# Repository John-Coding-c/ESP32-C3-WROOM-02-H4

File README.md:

# ESP32IoT sensor board

A compact, battery-powered, Wi-Fi/Bluetooth LE sensor board built around the
**ESP32-C3-WROOM-02-H4**. It logs temperature, humidity, pressure, light and sound,
stores data on a microSD card and external flash, and charges a single-cell LiPo
from USB-C. The same USB-C port programs the ESP32 automatically.

## Features

**Board**
- 4-layer PCB, 1.6 mm thick, **90 x 53 mm**
- 90 components, 79 nets, 985 track segments, 167 vias
- Single-sided assembly (all parts on the top side), 0805 passives

**Processing and wireless**
- ESP32-C3-WROOM-02-H4: 32-bit RISC-V at up to 160 MHz, 4 MB flash, 2.4 GHz Wi-Fi (802.11 b/g/n) and Bluetooth 5 LE, on-module antenna
- Extra W25Q32JVSSIQ SPI flash: 32 Mbit (4 MB)
- microSD slot on the SPI bus, with test points on MOSI, MISO, SCLK, CS and CS_SD

**Sensors**
- BME280: temperature, humidity and barometric pressure over I2C (4.7 kOhm pull-ups on SDA/SCL)
- TEMT6000X01 ambient-light phototransistor, read on an ADC pin
- CMC-5042PF-AC electret microphone with a MAX4466 amplifier and a 100 kOhm gain trimmer (R17)

**Power**
- USB-C input, 5 V, with a 1.1 A resettable fuse (F1) and USBLC6-2SC6 ESD protection on D+/D-
- MCP73871 LiPo charger with power-path management: fast-charge current about 500 mA (R5 = 2 kOhm), status on 3 LEDs (charging, charged, power good)
- LM1117-3.3 regulator, 800 mA rating, feeding the 3.3 V rail
- JST-PH 2 mm connector for a single-cell LiPo
- Ferrite bead (FB1) between the charger output and the 5 V rail

**USB and programming**
- CP2102N USB-to-UART bridge
- Auto-reset and auto-boot circuit (2 BC817 transistors on DTR/RTS) so the ESP32 programs over USB with no button presses
- EN (reset) and BOOT push-buttons

**Expansion and indicators**
- 4-pin I2C header (3V3, GND, SDA, SCL)
- 5-pin GPIO header (GPIO8, GPIO18, GPIO19, 3V3, GND)
- 6 LEDs: 3 charger status, 1 power, 1 UART TX, 1 UART RX
- 5 test points for the SPI signals

## Gallery

| Top | Bottom |
|---|---|
|  |  |

## Schematics

| Sheet | File |
|---|---|
| Power, charger and regulator | [01-power-and-charging.png](docs/schematics/01-power-and-charging.png) |
| ESP32-C3, USB bridge, flash, SD card | [02-esp32-c3-and-usb.png](docs/schematics/02-esp32-c3-and-usb.png) |
| Sensors (BME280, light, microphone) | [03-sensors.png](docs/schematics/03-sensors.png) |
| User interface (buttons, auto-reset, headers) | [04-user-interface.png](docs/schematics/04-user-interface.png) |

### Power and charging

### ESP32-C3, USB and storage

### Sensors

### User interface

## Direct Memory Access

uses the ESP32-C3's DMA for the SPI flash, the microSD card and the light sensor. 

```
cd firmware
idf.py set-target esp32c3
idf.py build flash monitor
```

## Project files

| Path | Contents |
|---|---|
| `ESP32IoT.kicad_pro` | KiCad 10 project |
| `ESP32IoT.kicad_sch` + `esp32-c3-02`, `sensors`, `user_interface` sheets | Hierarchical schematic |
| `ESP32IoT.kicad_pcb` | Routed 4-layer board |
| `Symbols/`, `Footprints/`, `3D models/` | Project libraries |
| `firmware/` | ESP-IDF test firmware using GDMA (SPI flash, SD card, ADC) |
| `BOM.ods`, `BOM11.xlsx` | Bill of materials |
| `docs/` | Renders and schematic images used by this README (`docs/schematics/ESP32IoT-schematic.pdf` is the full vector schematic) |

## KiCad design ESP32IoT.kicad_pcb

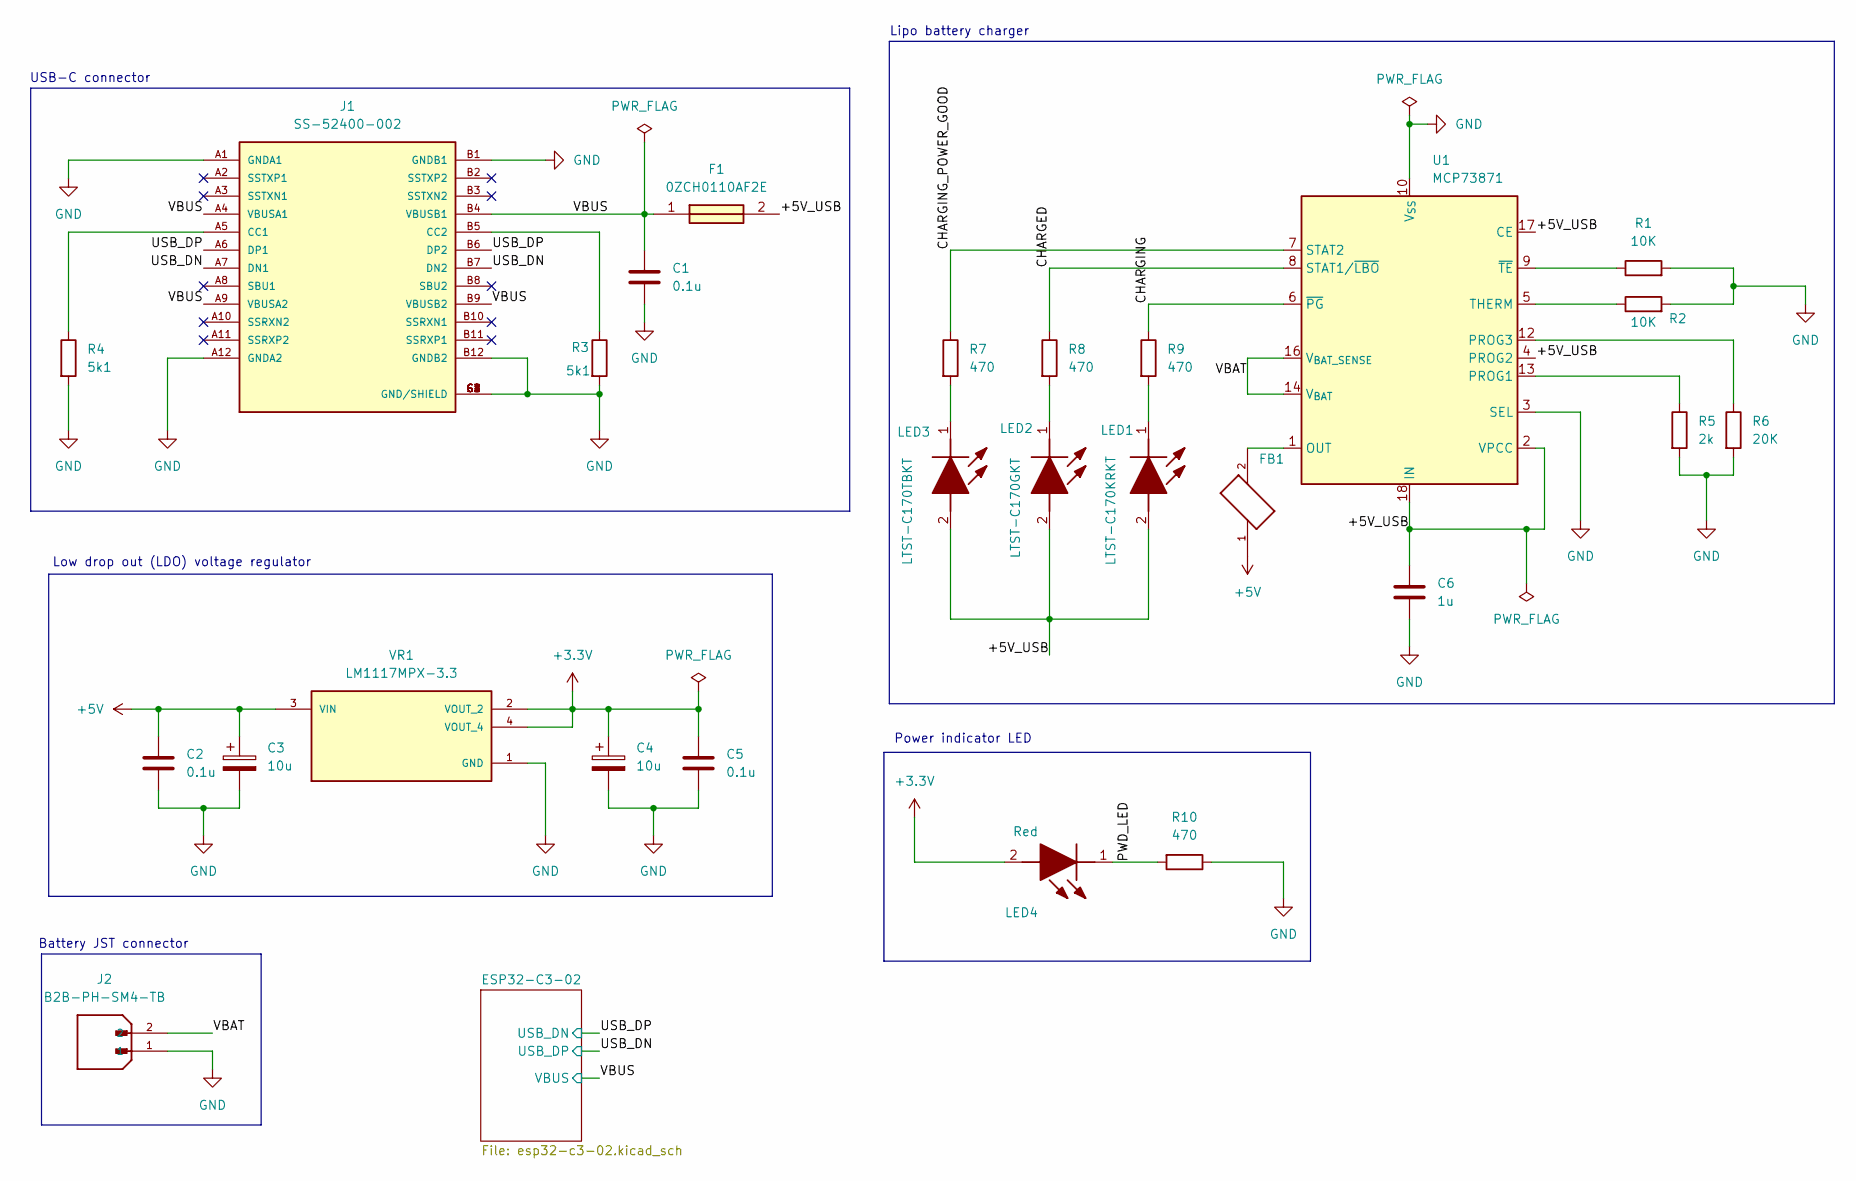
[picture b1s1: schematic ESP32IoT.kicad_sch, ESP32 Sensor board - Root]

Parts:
C1, C2, C5: 0.1u; C_0805_2012Metric
C3, C4: 10u; T491A
C6: 1u; C_0805_2012Metric
F1: 0ZCH0110AF2E; FUSC3226X100N; Manufacturer_Part_Number 0ZCH0110AF2E
FB1: FBMJ2125HM330-T; BEADC2012X105N
J1: SS-52400-002; BELFUSE_SS-52400-002; PARTREV A0
J2: B2B-PH-SM4-TB; JST_B2B-PH-SM4-TB; PARTREV N/A
LED1: LTST-C170KRKT; LEDC2012X120N; Manufacturer_Part_Number LTST-C170KRKT; Mouser Part Number 859-LTST-C170KRKT
LED2: LTST-C170GKT; LEDC2012X120N; Manufacturer_Part_Number LTST-C170GKT; Mouser Part Number 859-LTST-C170GKT
LED3: LTST-C170TBKT; LEDC2012X120N; Manufacturer_Part_Number LTST-C170TBKT; Mouser Part Number 859-LTST-C170TBKT
LED4: Red; LEDC2012X120N; Manufacturer_Part_Number LTST-C170KRKT; Mouser Part Number 859-LTST-C170KRKT
R1, R2: 10K; R_0805_2012Metric
R3, R4: 5k1; R_0805_2012Metric
R5: 2k; R_0805_2012Metric
R6: 20K; R_0805_2012Metric
R7, R8, R9, R10: 470; R_0805_2012Metric
U1: MCP73871; QFN-20-1EP_4x4mm_P0.5mm_EP2.5x2.5mm
VR1: LM1117MPX-3.3; VREG_LM1117MPX-3.3

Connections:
+3.3V: C4.1, C5.1, LED4.2 (A), VR1.2 (VOUT_2), VR1.4 (VOUT_4); also elsewhere on the board
+5V: C2.1, C3.1, FB1.1, VR1.3 (VIN)
/+5V_USB: C6.1, F1.2, LED1.2 (A), LED2.2 (A), LED3.2 (A), U1.2 (VPCC), U1.4 (PROG2), U1.17 (CE), U1.18 (IN), U1.19 (IN)
/CHARGED: R8.1, U1.8 (STAT1/~LBO)
/CHARGING: R9.1, U1.6 (~PG)
/CHARGING_POWER_GOOD: R7.1, U1.7 (STAT2)
/PWD_LED: LED4.1 (K), R10.2
/USB_DN: J1.A7 (DN1), J1.B7 (DN2); also elsewhere on the board
/USB_DP: J1.A6 (DP1), J1.B6 (DP2); also elsewhere on the board
/VBAT: J2.2, U1.14 (V_{BAT}), U1.15 (V_{BAT}), U1.16 (V_{BAT_SENSE})
/VBUS: C1.1, F1.1, J1.A4 (VBUSA1), J1.A9 (VBUSA2), J1.B4 (VBUSB1), J1.B9 (VBUSB2); also elsewhere on the board
GND: C1.2, C2.2, C3.2, C4.2, C5.2, C6.2, J1.A1 (GNDA1), J1.A12 (GNDA2), J1.B1 (GNDB1), J1.B12 (GNDB2), J1.G1 (GND/SHIELD), J1.G2 (GND/SHIELD), J1.G3 (GND/SHIELD), J1.G4 (GND/SHIELD), J1.S1 (GND/SHIELD), J1.S2 (GND/SHIELD), J1.S3 (GND/SHIELD), J1.S4 (GND/SHIELD), J2.1, R1.2, R2.2, R3.2, R4.2, R5.2, R6.2, R10.1, U1.3 (SEL), U1.10 (V_{SS}), U1.11 (V_{SS}), U1.21 (V_{SS}), VR1.1 (GND); also elsewhere on the board
unnamed: FB1.2, U1.1 (OUT), U1.20 (OUT)
unnamed: J1.A5 (CC1), R4.1
unnamed: J1.B5 (CC2), R3.1
unnamed: LED1.1 (K), R9.2
unnamed: LED2.1 (K), R8.2
unnamed: LED3.1 (K), R7.2
unnamed: R5.1, U1.13 (PROG1)
unnamed: R6.1, U1.12 (PROG3)
unnamed: R2.1, U1.5 (THERM)
unnamed: R1.1, U1.9 (~TE)

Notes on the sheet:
USB-C connector
Power indicator LED
Lipo battery charger
Battery JST connector
Low drop out (LDO) voltage regulator

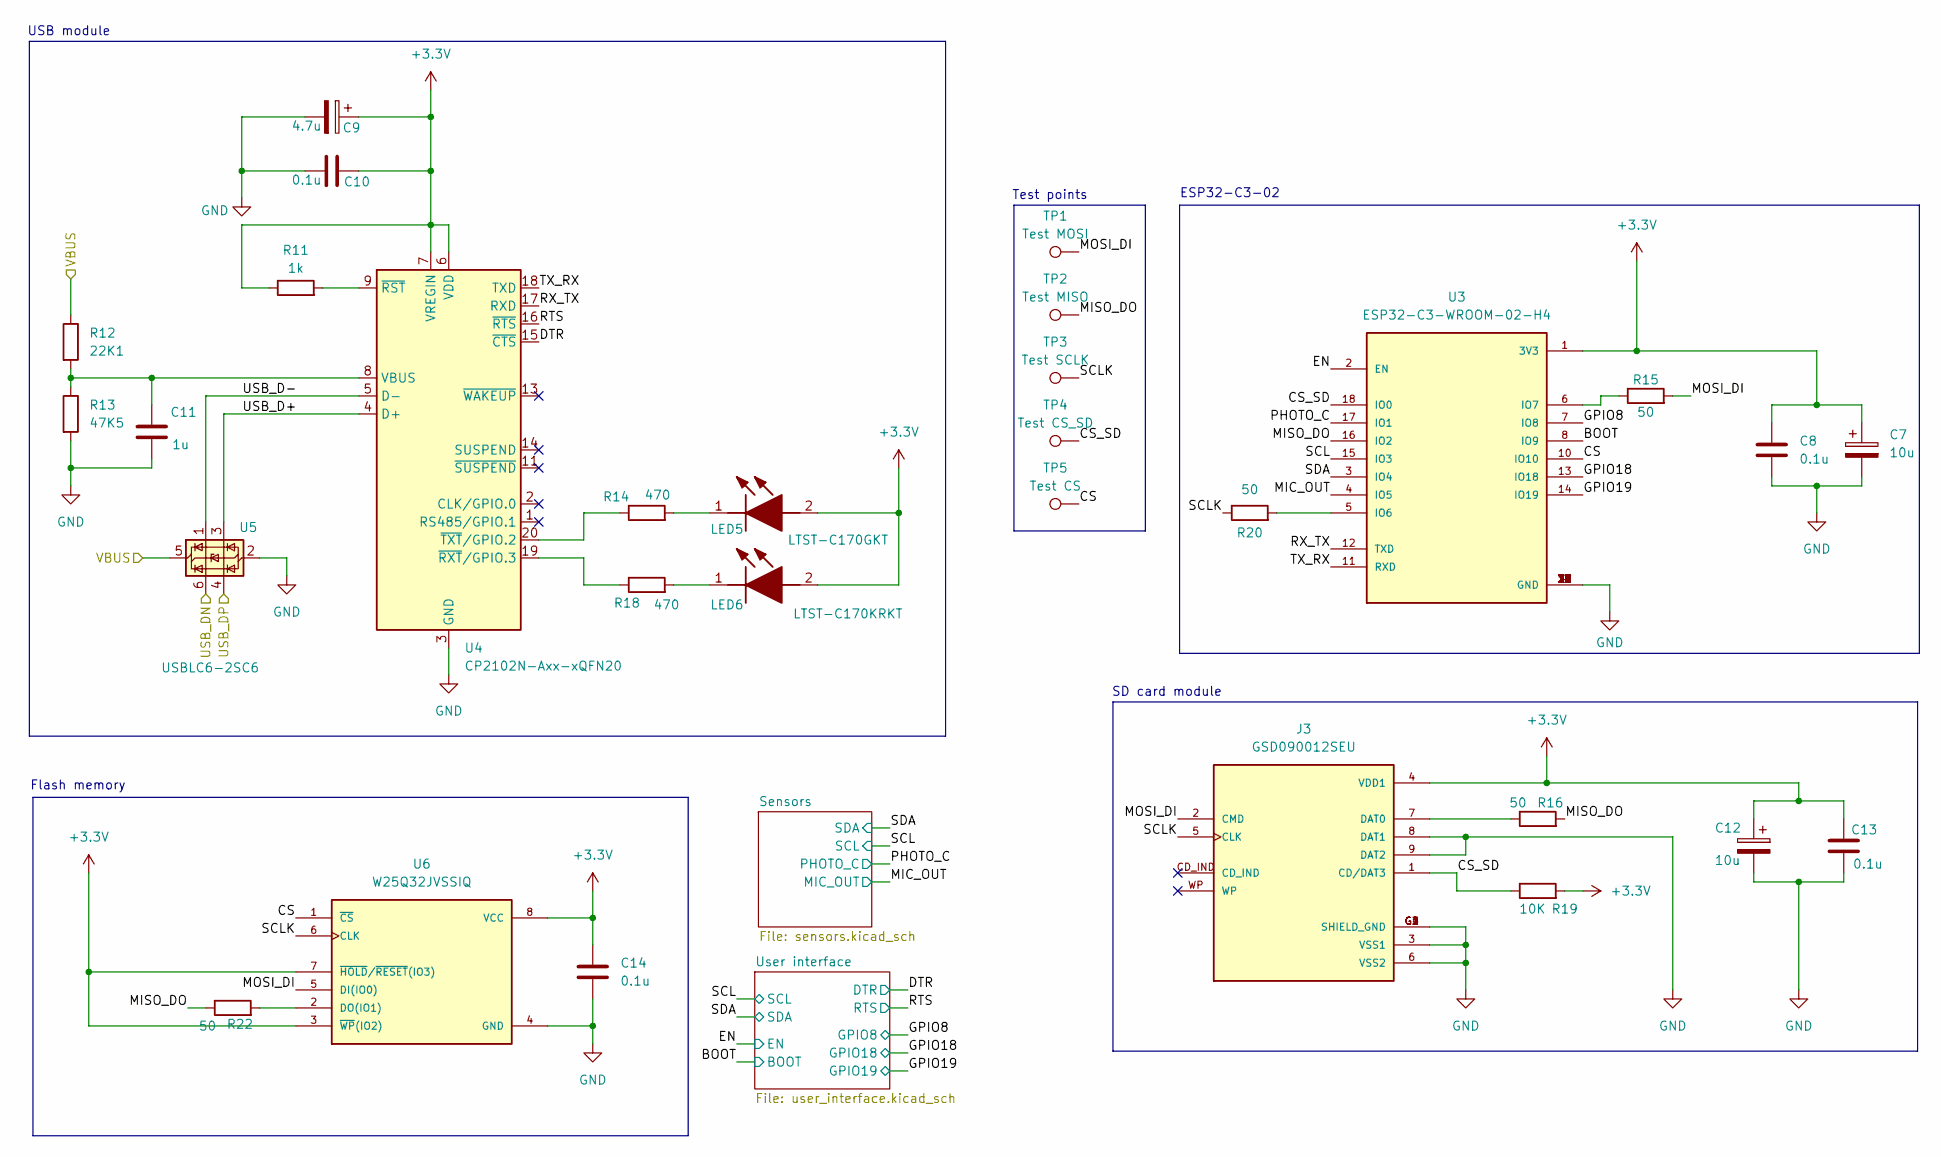
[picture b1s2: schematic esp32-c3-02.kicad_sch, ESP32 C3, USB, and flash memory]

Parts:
C7, C12: 10u; T491A
C8, C10, C13, C14: 0.1u; C_0805_2012Metric
C9: 4.7u; T491A
C11: 1u; C_0805_2012Metric
J3: GSD090012SEU; AMPHENOL_GSD090012SEU; PARTREV E
LED5: LTST-C170GKT; LEDC2012X120N; Manufacturer_Part_Number LTST-C170GKT; Mouser Part Number 859-LTST-C170GKT
LED6: LTST-C170KRKT; LEDC2012X120N; Manufacturer_Part_Number LTST-C170KRKT; Mouser Part Number 859-LTST-C170KRKT
R11: 1k; R_0805_2012Metric
R12: 22K1; R_0805_2012Metric
R13: 47K5; R_0805_2012Metric
R14, R18: 470; R_0805_2012Metric
R15, R16, R20, R22: 50; R_0805_2012Metric
R19: 10K; R_0805_2012Metric
TP1: Test MOSI; TestPoint_Pad_D1.0mm
TP2: Test MISO; TestPoint_Pad_D1.0mm
TP3: Test SCLK; TestPoint_Pad_D1.0mm
TP4: Test CS_SD; TestPoint_Pad_D1.0mm
TP5: Test CS; TestPoint_Pad_D1.0mm
U3: ESP32-C3-WROOM-02-H4; MODULE_ESP32-C3-WROOM-02-H4
U4: CP2102N-Axx-xQFN20; SiliconLabs_QFN-20-1EP_3x3mm_P0.5mm_EP1.8x1.8mm
U5: USBLC6-2SC6; SOT-23-6
U6: W25Q32JVSSIQ; SOIC127P790X216-8N; M_PART_NUMBER W25QXX

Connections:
+3.3V: C7.1, C8.1, C9.1, C10.2, C12.1, C13.1, C14.1, J3.4 (VDD1), LED5.2 (A), LED6.2 (A), R11.1, R19.2, U3.1 (3V3), U4.6 (VDD), U4.7 (VREGIN), U6.3 (~WP(IO2)), U6.7 (~HOLD/~RESET(IO3)), U6.8 (VCC); also elsewhere on the board
/ESP32-C3-02/BOOT: U3.8 (IO9); also elsewhere on the board
/ESP32-C3-02/CS: TP5.1 (1_1), U3.10 (IO10), U6.1 (~CS)
/ESP32-C3-02/CS_SD: J3.1 (CD/DAT3), R19.1, TP4.1 (1_1), U3.18 (IO0)
/ESP32-C3-02/DTR: U4.15 (~CTS); also elsewhere on the board
/ESP32-C3-02/EN: U3.2 (EN); also elsewhere on the board
/ESP32-C3-02/GPIO8: U3.7 (IO8); also elsewhere on the board
/ESP32-C3-02/GPIO18: U3.13 (IO18); also elsewhere on the board
/ESP32-C3-02/GPIO19: U3.14 (IO19); also elsewhere on the board
/ESP32-C3-02/MIC_OUT: U3.4 (IO5); also elsewhere on the board
/ESP32-C3-02/MISO_DO: R16.2, R22.1, TP2.1 (1_1), U3.16 (IO2)
/ESP32-C3-02/MOSI_DI: J3.2 (CMD), R15.2, TP1.1 (1_1), U6.5 (DI(IO0))
/ESP32-C3-02/PHOTO_C: U3.17 (IO1); also elsewhere on the board
/ESP32-C3-02/RTS: U4.16 (~RTS); also elsewhere on the board
/ESP32-C3-02/RX_TX: U3.12 (TXD), U4.17 (RXD)
/ESP32-C3-02/SCL: U3.15 (IO3); also elsewhere on the board
/ESP32-C3-02/SCLK: J3.5 (CLK), R20.1, TP3.1 (1_1), U6.6 (CLK)
/ESP32-C3-02/SDA: U3.3 (IO4); also elsewhere on the board
/ESP32-C3-02/TX_RX: U3.11 (RXD), U4.18 (TXD)
/ESP32-C3-02/USB_D+: U4.4 (D+), U5.3 (I/O2)
/ESP32-C3-02/USB_D-: U4.5 (D-), U5.1 (I/O1)
/USB_DN: U5.4 (I/O2); also elsewhere on the board
/USB_DP: U5.6 (I/O1); also elsewhere on the board
/VBUS: R12.1, U5.5 (VBUS); also elsewhere on the board
GND: C7.2, C8.2, C9.2, C10.1, C11.2, C12.2, C13.2, C14.2, J3.3 (VSS1), J3.6 (VSS2), J3.8 (DAT1), J3.9 (DAT2), J3.G1 (SHIELD_GND), J3.G2 (SHIELD_GND), J3.G3 (SHIELD_GND), J3.G4 (SHIELD_GND), R13.2, U3.9 (GND), U3.19 (GND), U3.20 (GND), U3.21 (GND), U3.22 (GND), U3.23 (GND), U3.24 (GND), U3.25 (GND), U3.26 (GND), U3.27 (GND), U3.28 (GND), U3.29 (GND), U3.30 (GND), U3.31 (GND), U3.32 (GND), U3.33 (GND), U3.34 (GND), U3.35 (GND), U3.36 (GND), U3.37 (GND), U3.38 (GND), U3.39 (GND), U4.3 (GND), U4.12 (GND), U4.21 (GND), U5.2 (GND), U6.4 (GND); also elsewhere on the board
unnamed: J3.7 (DAT0), R16.1
unnamed: LED5.1 (K), R14.2
unnamed: LED6.1 (K), R18.2
unnamed: R20.2, U3.5 (IO6)
unnamed: R15.1, U3.6 (IO7)
unnamed: C11.1, R12.2, R13.1, U4.8 (VBUS)
unnamed: R11.2, U4.9 (~RST)
unnamed: R18.1, U4.19 (~RXT/GPIO.3)
unnamed: R14.1, U4.20 (~TXT/GPIO.2)
unnamed: R22.2, U6.2 (DO(IO1))

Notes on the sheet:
SD card module
Flash memory
Test points
ESP32-C3-02
USB module

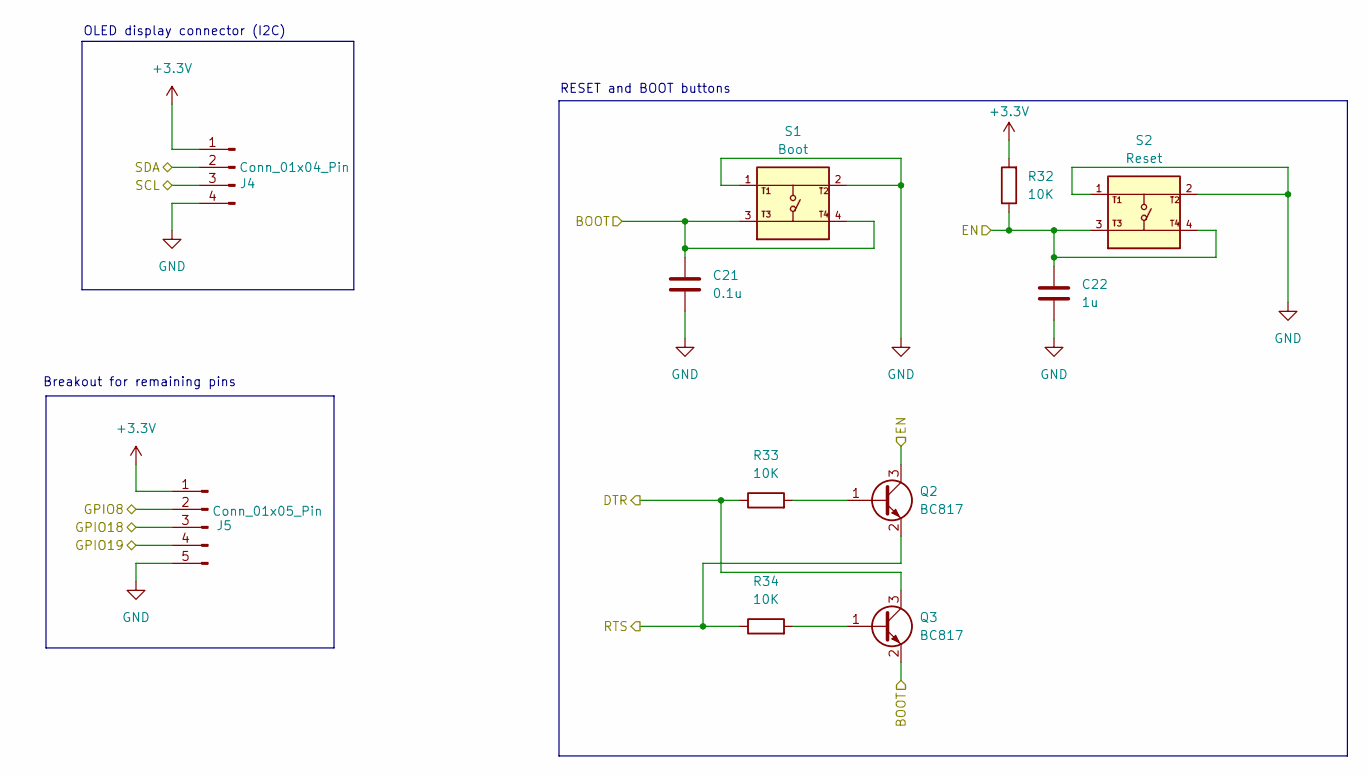
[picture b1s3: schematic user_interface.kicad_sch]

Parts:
C21: 0.1u; C_0805_2012Metric
C22: 1u; C_0805_2012Metric
J4: Conn_01x04_Pin; PinHeader_1x04_P2.54mm_Vertical
J5: Conn_01x05_Pin; PinHeader_1x05_P2.54mm_Vertical
Q2, Q3: BC817; SOT-23
R32, R33, R34: 10K; R_0805_2012Metric
S1: Boot; SW_USLPT2819DT2TR; PARTREV P
S2: Reset; SW_USLPT2819DT2TR; PARTREV P

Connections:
+3.3V: J4.1, J5.1, R32.2; also elsewhere on the board
/ESP32-C3-02/BOOT: C21.1, Q3.2 (E), S1.3, S1.4; also elsewhere on the board
/ESP32-C3-02/DTR: Q3.3 (C), R33.1; also elsewhere on the board
/ESP32-C3-02/EN: C22.1, Q2.3 (C), R32.1, S2.3, S2.4; also elsewhere on the board
/ESP32-C3-02/GPIO8: J5.2; also elsewhere on the board
/ESP32-C3-02/GPIO18: J5.3; also elsewhere on the board
/ESP32-C3-02/GPIO19: J5.4; also elsewhere on the board
/ESP32-C3-02/RTS: Q2.2 (E), R34.1; also elsewhere on the board
/ESP32-C3-02/SCL: J4.3; also elsewhere on the board
/ESP32-C3-02/SDA: J4.2; also elsewhere on the board
GND: C21.2, C22.2, J4.4, J5.5, S1.1, S1.2, S2.1, S2.2; also elsewhere on the board
unnamed: Q2.1 (B), R33.2
unnamed: Q3.1 (B), R34.2

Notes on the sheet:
OLED display connector (I2C)
RESET and BOOT buttons
Breakout for remaining pins

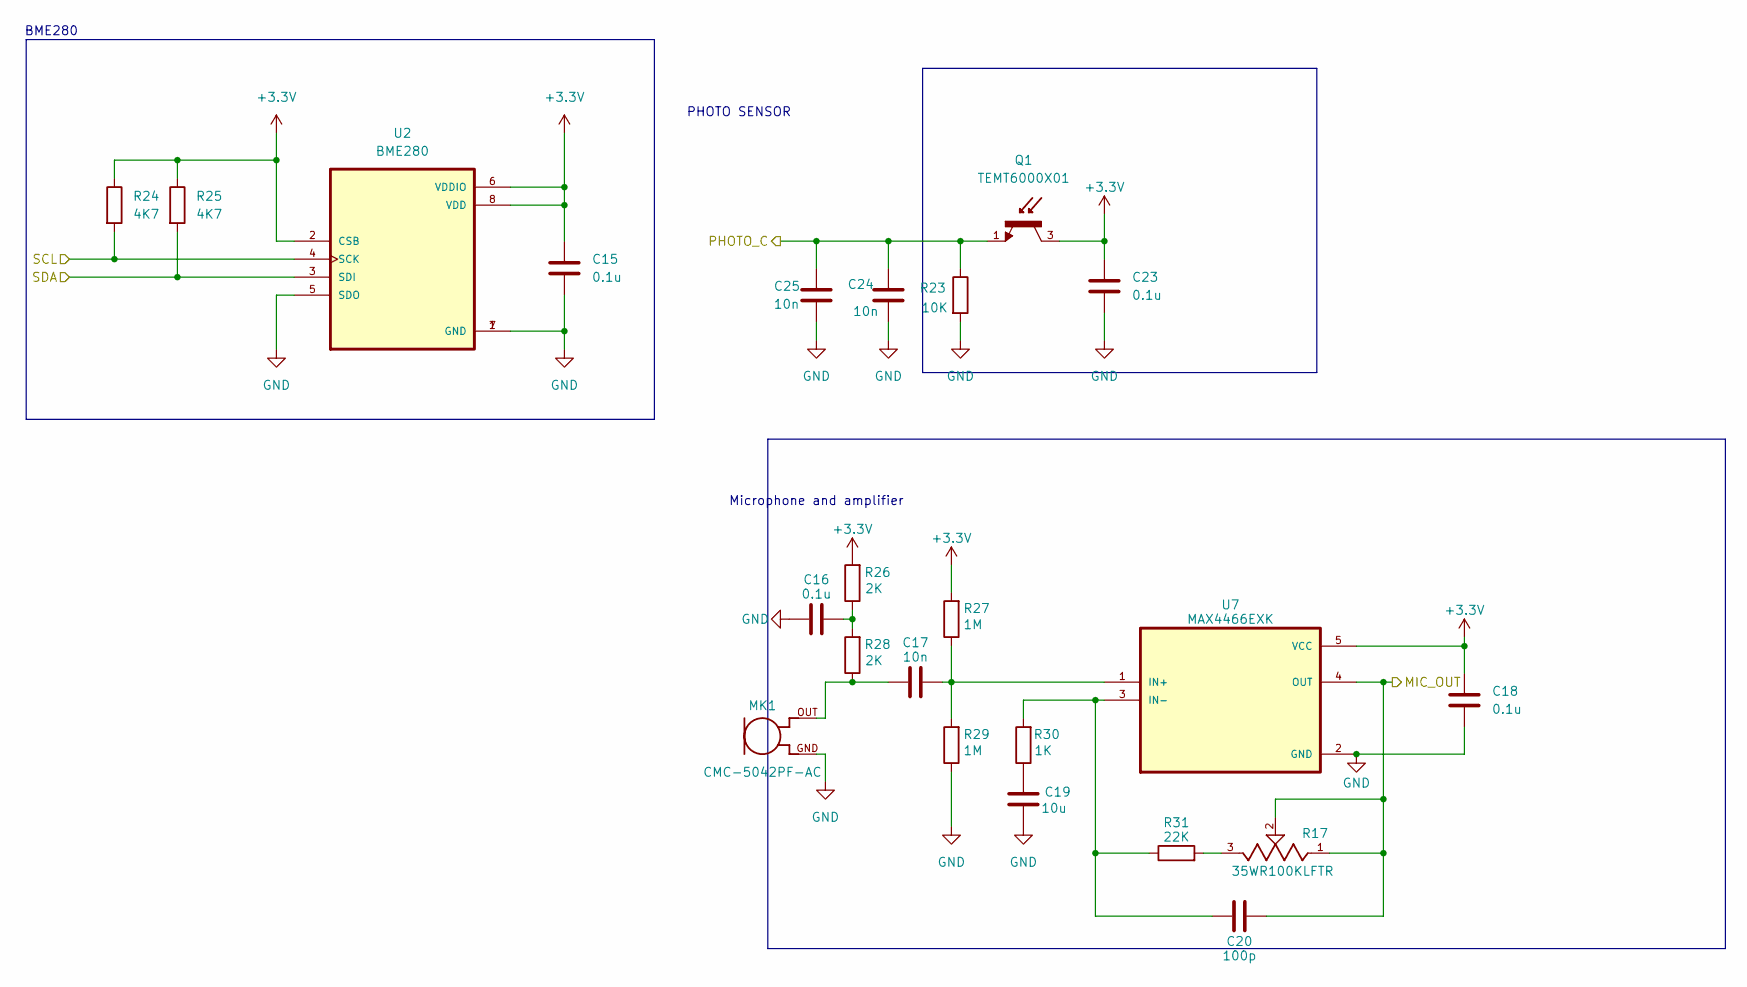
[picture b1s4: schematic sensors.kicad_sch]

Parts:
C15, C16, C18, C23: 0.1u; C_0805_2012Metric
C17, C24, C25: 10n; C_0805_2012Metric
C19: 10u; C_0805_2012Metric
C20: 100p; C_0805_2012Metric
MK1: CMC-5042PF-AC; CUI_CMC-5042PF-AC; Manufacturer_Part_Number CMC-5042PF-AC
Q1: TEMT6000X01; TRANS_TEMT6000X01; PARTREV 1.9
R17: 35WR100KLFTR; TRIM_35WR100KLFTR; PARTREV D
R23: 10K; R_0805_2012Metric
R24, R25: 4K7; R_0805_2012Metric
R26, R28: 2K; R_0805_2012Metric
R27, R29: 1M; R_0805_2012Metric
R30: 1K; R_0805_2012Metric
R31: 22K; R_0805_2012Metric
U2: BME280; PSON65P250X250X100-8N
U7: MAX4466EXK; SOT65P210X110-5N; Manufacturer_Part_Number MAX4466EXK

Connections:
+3.3V: C15.1, C18.1, C23.1, Q1.3, R24.1, R25.1, R26.2, R27.2, U2.2 (CSB), U2.6 (VDDIO), U2.8 (VDD), U7.5 (VCC); also elsewhere on the board
/ESP32-C3-02/MIC_OUT: C20.2, R17.1, R17.2, U7.4 (OUT); also elsewhere on the board
/ESP32-C3-02/PHOTO_C: C24.1, C25.1, Q1.1, R23.1; also elsewhere on the board
/ESP32-C3-02/SCL: R24.2, U2.4 (SCK); also elsewhere on the board
/ESP32-C3-02/SDA: R25.2, U2.3 (SDI); also elsewhere on the board
GND: C15.2, C16.2, C18.2, C19.1, C23.2, C24.2, C25.2, MK1.GND, R23.2, R29.1, U2.1 (GND), U2.5 (SDO), U2.7 (GND), U7.2 (GND); also elsewhere on the board
unnamed: C16.1, R26.1, R28.2
unnamed: C17.2, MK1.OUT, R28.1
unnamed: C19.2, R30.1
unnamed: R17.3, R31.2
unnamed: C17.1, R27.1, R29.2, U7.1 (IN+)
unnamed: C20.1, R30.2, R31.1, U7.3 (IN-)

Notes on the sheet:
BME280
PHOTO SENSOR
Microphone and amplifier

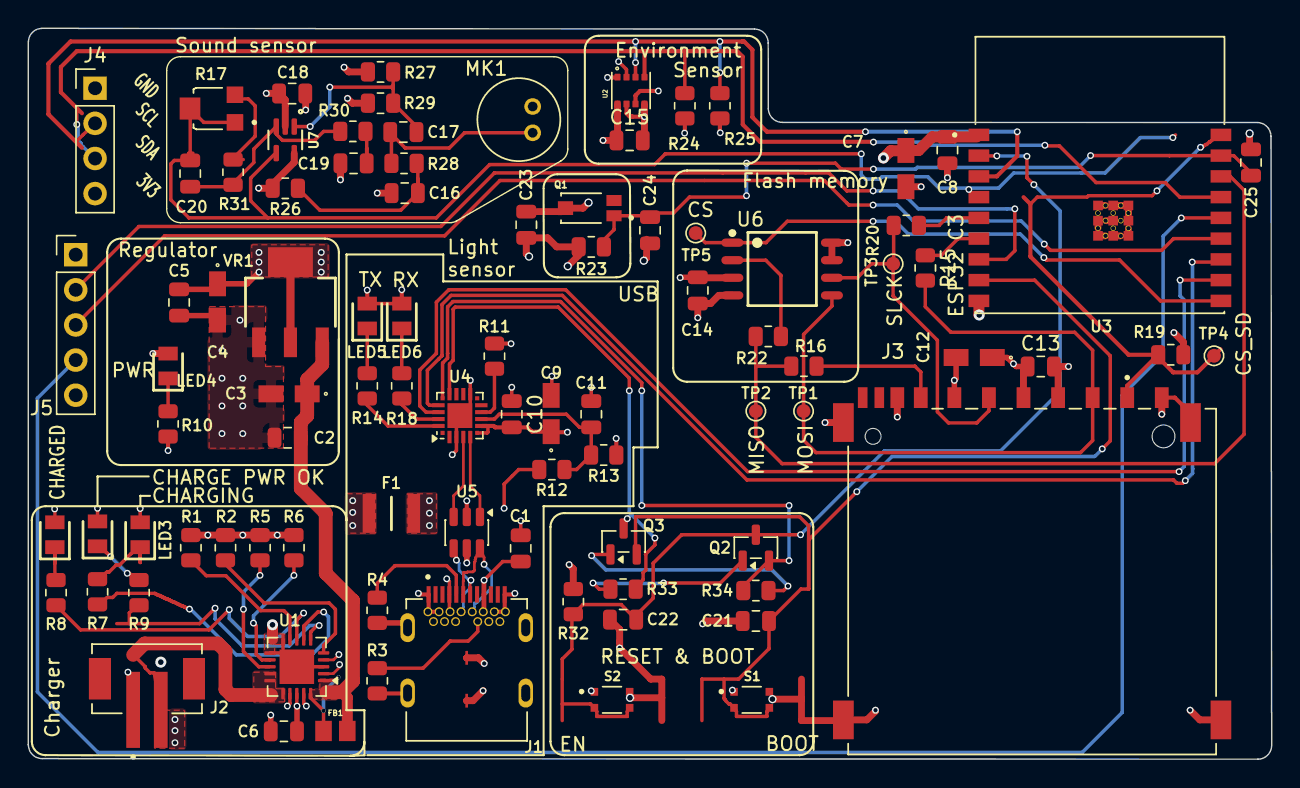
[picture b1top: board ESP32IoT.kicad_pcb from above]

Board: 4 copper layers, 89.9 x 52.8 mm, 90 parts (0 on the bottom side), 60 nets.

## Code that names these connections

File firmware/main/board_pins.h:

#pragma once
/* GPIO map taken from the routed PCB (ESP32IoT.kicad_pcb, U3 pad nets). */

/* Shared SPI bus: W25Q32 flash (U6) + microSD slot (J3). */
#define PIN_SPI_SCLK   6   /* module pad 5,  net SCLK    */
#define PIN_SPI_MOSI   7   /* module pad 6,  net MOSI_DI */
#define PIN_SPI_MISO   2   /* module pad 16, net MISO_DO (strapping pin) */
#define PIN_CS_FLASH   10  /* module pad 10, net CS      */
#define PIN_CS_SD      0   /* module pad 18, net CS_SD   */

/* I2C: BME280. The C3 I2C peripheral has no GDMA path. */
#define PIN_I2C_SDA    4
#define PIN_I2C_SCL    3

/* Analog. */
#define PIN_PHOTO      1   /* TEMT6000, ADC1_CH1: supports continuous (DMA) mode */
#define PIN_MIC        5   /* MAX4466,  ADC2_CH0: no ADC DMA on the C3           */
